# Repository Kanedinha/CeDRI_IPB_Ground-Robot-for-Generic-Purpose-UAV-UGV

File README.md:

# CeDRI_IPB_Ground-Robot-for-Generic-Purpose-UAV-UGV

Project for Master Degree Thesis

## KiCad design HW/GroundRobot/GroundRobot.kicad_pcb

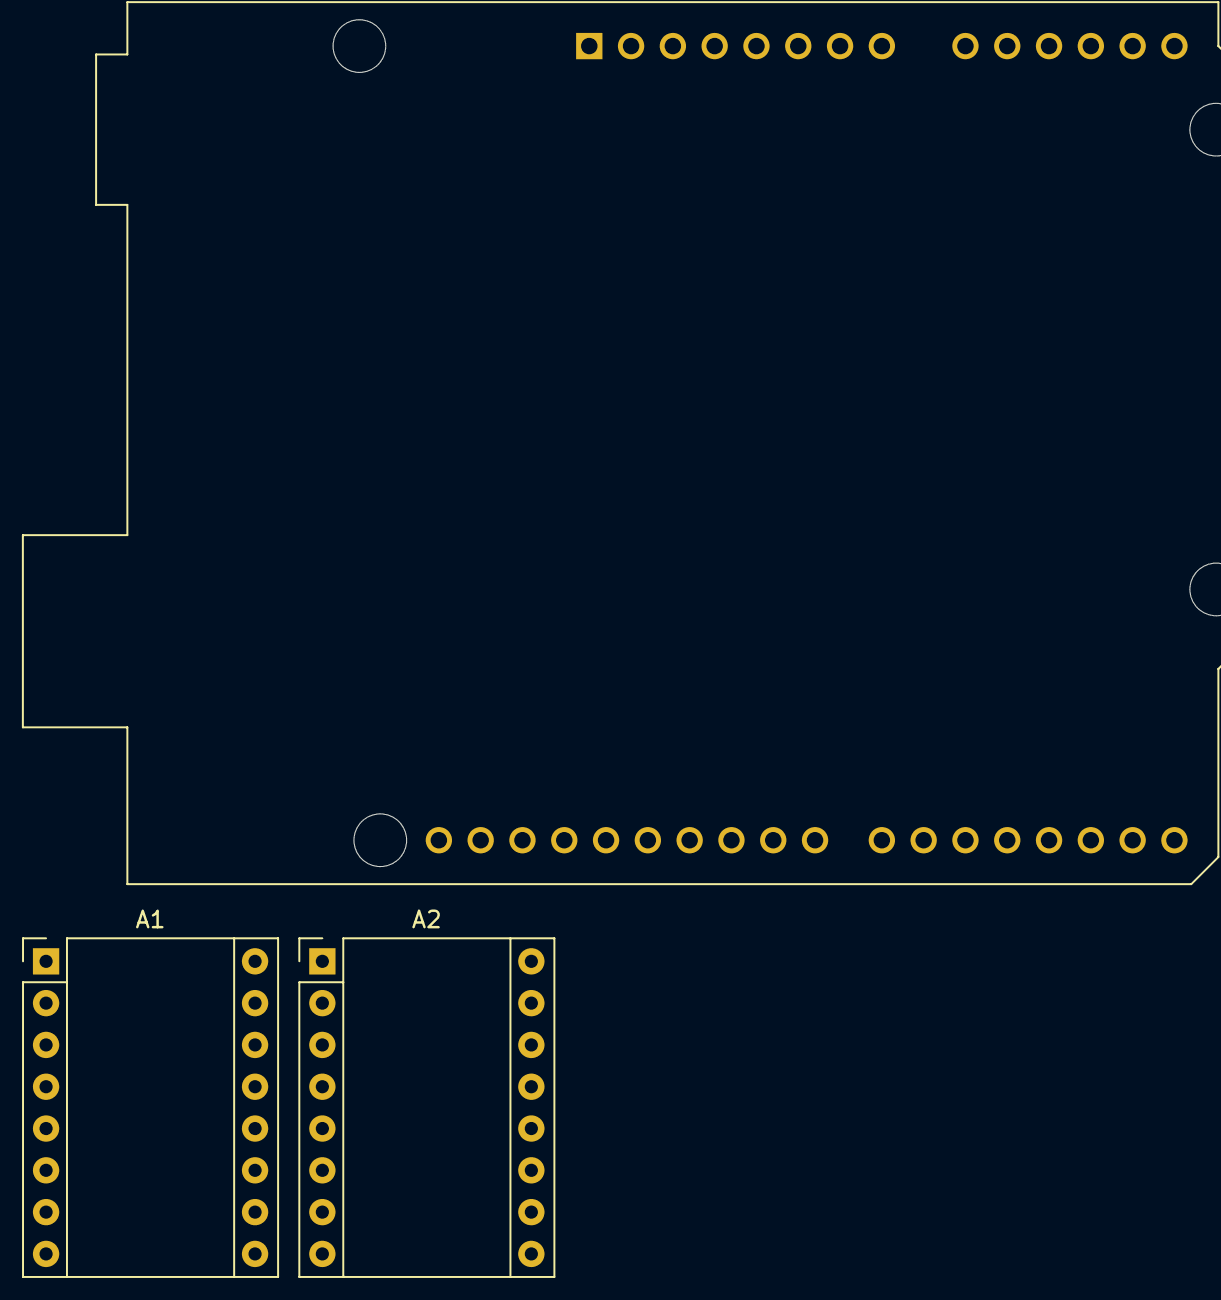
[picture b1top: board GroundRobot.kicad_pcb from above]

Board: 2 copper layers, 3 parts (0 on the bottom side), 7 nets, no tracks yet.

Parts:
A1: Roll; Pololu_Breakout-16_15.2x20.3mm
A2: Pitch; Pololu_Breakout-16_15.2x20.3mm
U1: ESP32; Arduino_UNO_R3_WithMountingHoles

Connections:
/Motor Drivers/+5V: A1.9 (~EN), A2.9 (~EN)
/Motor Drivers/GND: A1.1 (GND), A1.7 (GND), A2.1 (GND), A2.7 (GND)
/Motor Drivers/Pitch Step: A2.15 (STEP), U1.20 (MTCK/GPIO13/ADC2_CH4)
/Motor Drivers/Roll Direction: A1.16 (DIR), U1.18 (MTDI/GPIO12/ADC2_CH5)
/Motor Drivers/Roll Step: A1.15 (STEP), U1.17 (MTMS/GPIO14/ADC2_CH6)
/Motor Drivers/VMOT: A1.8 (VMOT), A2.8 (VMOT)
unnamed: U1.3 (VDD3P3), U1.4 (VDD3P3)

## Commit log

2023-10-23 Platform idea
    2 DOF platform, need step motors and a junction with 2 DOF too
2023-10-23 working
2023-10-23 Articles and articles to read until die
    Yeeeeyyy
2023-10-26 Starting with Motor control
2023-10-26 saving
2023-10-26 Teste bim bim bambam
2023-10-27 how to read the enconder corractly?
2023-10-30 try solve the wtd int error
2023-11-06 wtd timer fixed
2023-11-06 sample rate 40kHz but wtd is a problem
2023-11-07 with RTOS
2023-11-08 with arduino framework
2023-11-08 teste pulse
2023-11-08 assets
2023-11-14 PD control working (also PID 2)
2023-11-16 more draws
2023-11-16 BTS7960
2023-11-20 code with coment each pin in each wire
2023-11-24 testing K_ff values
2023-11-27 Kff test
2023-11-30 more articles
2023-12-05 serial
2024-02-07 oh my god a lot of things
2024-02-07 platform update
2024-02-22 Structure
2024-03-01 Main Update with filters
2024-03-25 update filters
2024-03-31 update articles
2024-04-30 update filters and STL files
2024-05-16 update articles and mechanic draws
2024-05-30 Update files
2024-06-10 update main with pitch and roll angles
2024-07-02 P controller
2024-07-08 Serial print problem
2024-07-08 data send solved
2024-07-10 Finish?
2024-07-10 just update DataSend function
2024-07-24 ROBOTS article and platform working
2024-09-24 update pcb and latex
2024-10-28 update dissertation
2024-11-04 Rename A_Single_Objective_Flower
2024-11-04 Rename An_Integration_Enhanced_Repetitive_Path_Planni
2024-11-04 Rename Autonomous_Landing_of_a_UAV_on_a_
2024-11-04 Rename Autonomous_Quadcopter_Precision_Landing_Onto_a_Heaving_Platform_New_Method_and_Experiment.pdf to Autonomous_Quadcopter_Precision_Landing.pdf
2024-11-04 Rename Ball_Balancing_on_a_Stewart_Platform_using_Fuzzy_Supervisory_PID_Visual_Servo_Control.pdf to Ball_Balancing_on_a_Stewart.pdf
2024-11-04 Rename Cooperative_Path_Planning_of_UAVs_amp_UGVs_for_a_Persistent_Surveillance_Task_in_Urban_Environments.pdf to Cooperative_Path_Planning_of_UAVs_amp_UGVs_for_a_Persiste.pdf
2024-11-04 Rename Cooperative_Relative_Pose_Estimation_to_Aid_Landing_of_an_Unmanned_Aerial_Vehicle_on_a_Moving_Platform.pdf to Cooperative_Relative.pdf
2024-11-04 Rename Cooperative_System_of_Ground_Robots_based_on_dynamic_exploration_of_Drone_Occupancy_Grid_Maps.pdf to Cooperative_System_of_.pdf
2024-11-04 Rename Design_and_Implementation_of_Autonomous_Takeoff_and_Landing_UAV_System_for_USV_Platform.pdf to Design_and_Implementation_of_Autonomous_Takeoff_and_Landing_UAV.pdf
2024-11-04 Rename Design_and_Implementation_of_Gimbal_on_Remotely_Operated_Vehicle_with_Fuzzy_Logic_Controller.pdf to Design_and_Implementation_of_Gimbal_on_Remotely.pdf
2024-11-04 update data
2024-11-04 update articles names
2024-11-05 clear main comments
2024-11-07 update testes
2024-11-20 update HW and tests
2024-11-21 images for thesis
2024-11-21 Rename imagem.png to LongBracket.png
2024-11-21 image
2024-11-21 Rename imagem.png to Bracket.png
2024-11-21 CentralSupport
2024-11-21 Rename imagem.png to CentralSupport.png
2024-11-21 BatteryHandler
2024-11-21 Rename imagem.png to BatteryHandler.png
2024-11-21 JointCoupler
2024-11-21 Rename imagem.png to JointCoupler.png
2024-11-21 MotorHandler
2024-11-21 Rename imagem.png to MotorHandler.png
2024-11-21 platform2
2024-11-21 Rename imagem.png to platform2.png
2024-11-21 platform1
2024-11-21 Rename imagem.png to platform1.png
2024-11-21 uJoint
2024-11-21 Update Solid Files
2024-11-21 NEMA17 Files
2024-12-02 update calibration
2024-12-03 update latex thesis
2024-12-11 update figs and latex thesis
2024-12-11 update thesis latex
2024-12-19 Final Update?
2025-01-09 Update Thesis Latex and Final paper
2025-01-09 update Latex
2025-02-03 Upload Thesis presentation
